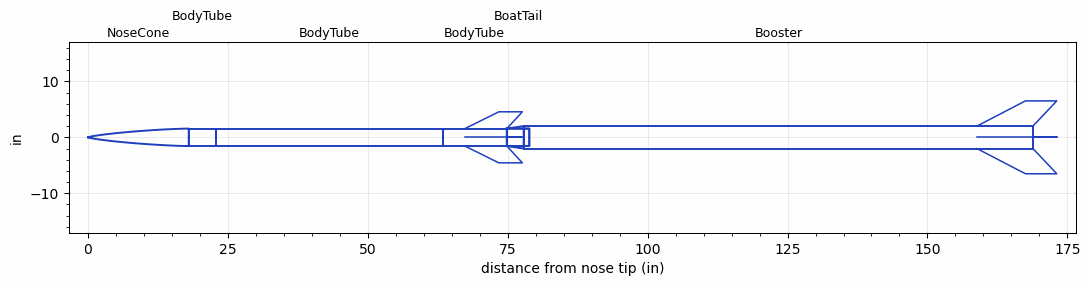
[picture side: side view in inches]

<RASAeroDocument>
 <FileVersion>2</FileVersion>
 <RocketDesign>
  <NoseCone>
   <Length>18</Length>
   <Diameter>3.12</Diameter>
   <Shape>Von Karman Ogive</Shape>
   <BluntRadius>0.1</BluntRadius>
   <Location>0</Location>
  </NoseCone>
  <BodyTube>
   <Length>4.85</Length>
   <Diameter>3.12</Diameter>
   <Location>18</Location>
  </BodyTube>
  <BodyTube>
   <Length>40.5</Length>
   <Diameter>3.12</Diameter>
   <Location>22.85</Location>
  </BodyTube>
  <BodyTube>
   <Length>11.5</Length>
   <Diameter>3.12</Diameter>
   <Location>63.35</Location>
   <BoattailLength>4</BoattailLength>
   <BoattailRearDiameter>3.11</BoattailRearDiameter>
   <Fin>
    <Count>4</Count>
    <Chord>7.5</Chord>
    <Span>3</Span>
    <SweepDistance>6.062</SweepDistance>
    <TipChord>4.2</TipChord>
    <Thickness>0.22</Thickness>
    <LERadius>0.05</LERadius>
    <Location>7.5</Location>
    <AirfoilSection>Hexagonal</AirfoilSection>
    <FX1>1</FX1>
    <FX3>1</FX3>
   </Fin>
  </BodyTube>
  <BoatTail>
   <Length>4</Length>
   <Diameter>3.12</Diameter>
   <RearDiameter>3.11</RearDiameter>
   <Location>74.85</Location>
  </BoatTail>
  <Booster>
   <Length>91</Length>
   <Diameter>4.02</Diameter>
   <InsideDiameter>3.12</InsideDiameter>
   <RailGuideDiameter>0.63</RailGuideDiameter>
   <RailGuideHeight>0.44</RailGuideHeight>
   <Location>74.85</Location>
   <ShoulderLength>3</ShoulderLength>
   <Fin>
    <Count>4</Count>
    <Chord>10</Chord>
    <Span>4.5</Span>
    <SweepDistance>8.66</SweepDistance>
    <TipChord>5.6</TipChord>
    <Thickness>0.22</Thickness>
    <LERadius>0.05</LERadius>
    <Location>10</Location>
    <AirfoilSection>Hexagonal</AirfoilSection>
    <FX1>1</FX1>
    <FX3>1</FX3>
   </Fin>
  </Booster>
  <Surface>Camouflage Paint</Surface>
  <ModifiedBarrowman>True</ModifiedBarrowman>
  <Turbulence>True</Turbulence>
  <UseBooster1>False</UseBooster1>
  <UseBooster2>False</UseBooster2>
 </RocketDesign>
 <LaunchSite>
  <Altitude>2000</Altitude>
  <Pressure>0</Pressure>
  <RodAngle>3</RodAngle>
  <RodLength>40</RodLength>
  <Temperature>50</Temperature>
  <WindSpeed>12</WindSpeed>
 </LaunchSite>
 <Recovery>
  <Altitude1>1000</Altitude1>
  <Altitude2>1000</Altitude2>
  <DeviceType1>None</DeviceType1>
  <DeviceType2>None</DeviceType2>
  <Event1>False</Event1>
  <Event2>False</Event2>
  <Size1>1</Size1>
  <Size2>1</Size2>
  <EventType1>None</EventType1>
  <EventType2>None</EventType2>
  <CD1>1.33</CD1>
  <CD2>1.33</CD2>
 </Recovery>
 <SimulationList>
  <Simulation>
   <SustainerEngine>M685W-PS  (AT)</SustainerEngine>
   <SustainerLaunchWt>25.8</SustainerLaunchWt>
   <SustainerNozzleDiameter>1.25</SustainerNozzleDiameter>
   <SustainerCG>50.34</SustainerCG>
   <SustainerIgnitionDelay>10</SustainerIgnitionDelay>
   <Booster1Engine>O5500X  (AT)</Booster1Engine>
   <Booster1LaunchWt>77.2</Booster1LaunchWt>
   <Booster1SeparationDelay>0</Booster1SeparationDelay>
   <Booster1IgnitionDelay>0</Booster1IgnitionDelay>
   <Booster1CG>105</Booster1CG>
   <Booster1NozzleDiameter>2.737</Booster1NozzleDiameter>
   <IncludeBooster1>True</IncludeBooster1>
   <Booster2Delay>0</Booster2Delay>
   <IncludeBooster2>False</IncludeBooster2>
   <TimetoApogee>90.52007</TimetoApogee>
   <MaxAltitude>115831.9</MaxAltitude>
   <MaxVelocity>2702.063</MaxVelocity>
  </Simulation>
 </SimulationList>
</RASAeroDocument>
